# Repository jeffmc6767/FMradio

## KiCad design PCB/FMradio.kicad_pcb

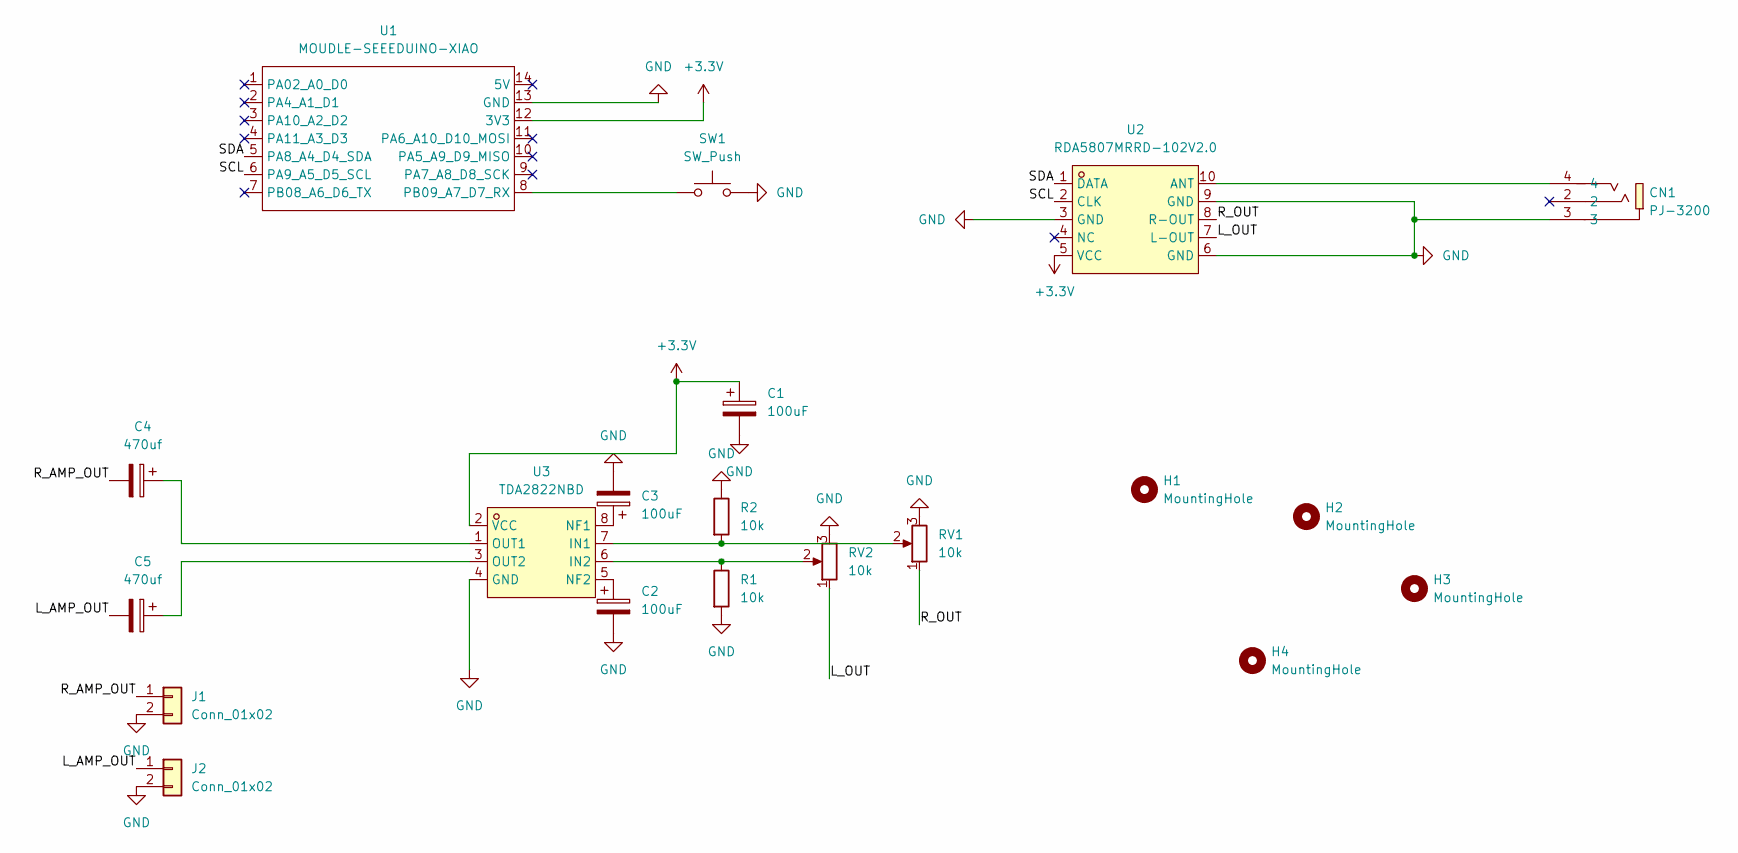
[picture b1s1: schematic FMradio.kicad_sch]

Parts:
C1, C2, C3: 100uF; CP_Radial_D6.3mm_P2.50mm
C4, C5: 470uf; CP_Radial_D6.3mm_P2.50mm
CN1: PJ-3200; AUDIO-TH_PJ-3200; MPN PJ-3200; LCSC Part C2689690
H1, H2, H3, H4: MountingHole; MountingHole_2.7mm_M2.5
J1, J2: Conn_01x02; PinHeader_1x02_P2.54mm_Vertical
R1, R2: 10k; R_Axial_DIN0207_L6.3mm_D2.5mm_P7.62mm_Horizontal
RV1, RV2: 10k; FanPinHeader_1x03_P2.54mm_Vertical
SW1: SW_Push; PinHeader_1x02_P2.54mm_Vertical
U1: MOUDLE-SEEEDUINO-XIAO; XIAO-RP2040-DIP
U2: RDA5807MRRD-102V2.0; RDA5807; MPN RDA5807MRRD-102V2.0; LCSC Part C9900205627
U3: TDA2822NBD; DIP-8_W7.62mm; MPN TDA2822NBD; LCSC Part C51927337

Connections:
+3.3V: C1.1, U1.12 (3V3), U2.5 (VCC), U3.2 (VCC)
/L_AMP_OUT: C5.2, J2.1
/L_OUT: RV2.1, U2.7 (L-OUT)
/R_AMP_OUT: C4.2, J1.1
/R_OUT: RV1.1, U2.8 (R-OUT)
/SCL: U1.6 (PA9_A5_D5_SCL), U2.2 (CLK)
/SDA: U1.5 (PA8_A4_D4_SDA), U2.1 (DATA)
GND: C1.2, C2.2, C3.2, CN1.3, J1.2, J2.2, R1.2, R2.1, RV1.3, RV2.3, SW1.2, U1.13 (GND), U2.3 (GND), U2.6 (GND), U2.9 (GND), U3.4 (GND)
unnamed: SW1.1, U1.8 (PB09_A7_D7_RX)
unnamed: CN1.4, U2.10 (ANT)
unnamed: R2.2, RV1.2, U3.7 (IN1)
unnamed: R1.1, RV2.2, U3.6 (IN2)
unnamed: C3.1, U3.8 (NF1)
unnamed: C2.1, U3.5 (NF2)
unnamed: C4.1, U3.1 (OUT1)
unnamed: C5.1, U3.3 (OUT2)

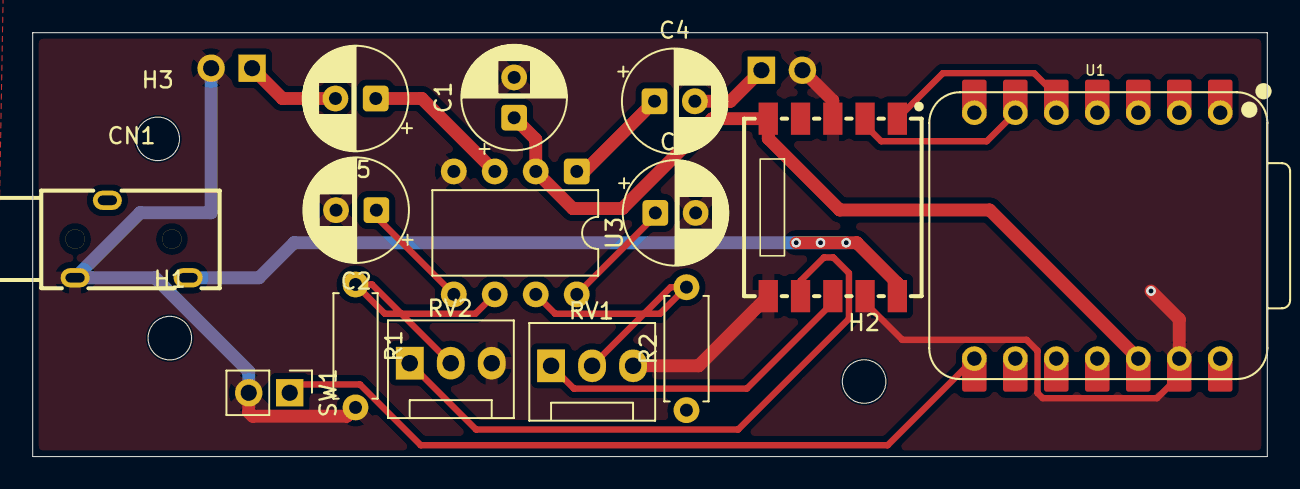
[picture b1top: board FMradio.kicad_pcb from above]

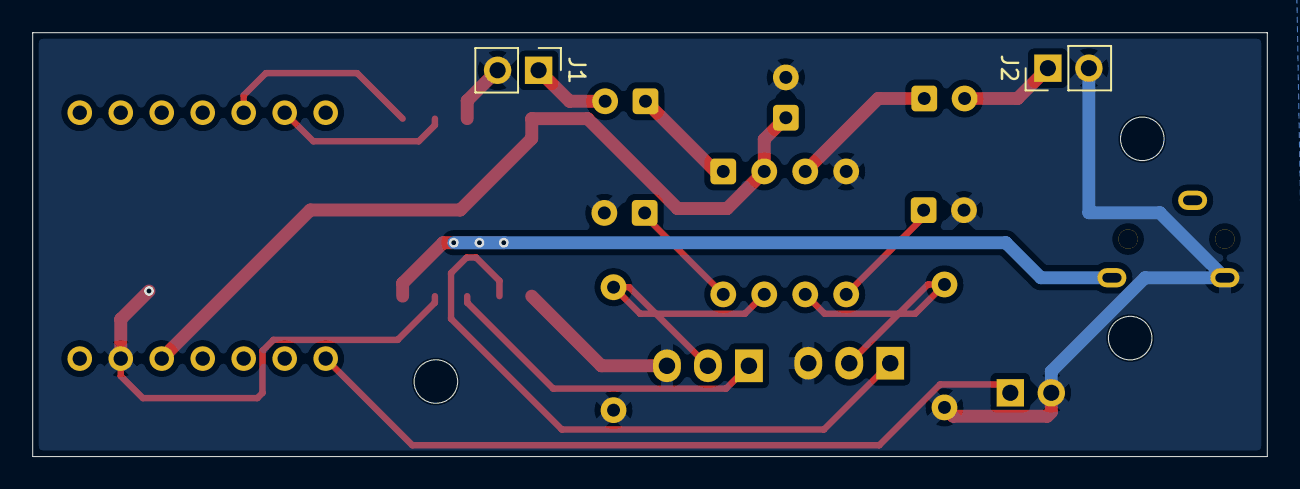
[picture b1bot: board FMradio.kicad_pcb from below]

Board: 2 copper layers, 76.5 x 26.3 mm, 19 parts (2 on the bottom side), 16 nets.
